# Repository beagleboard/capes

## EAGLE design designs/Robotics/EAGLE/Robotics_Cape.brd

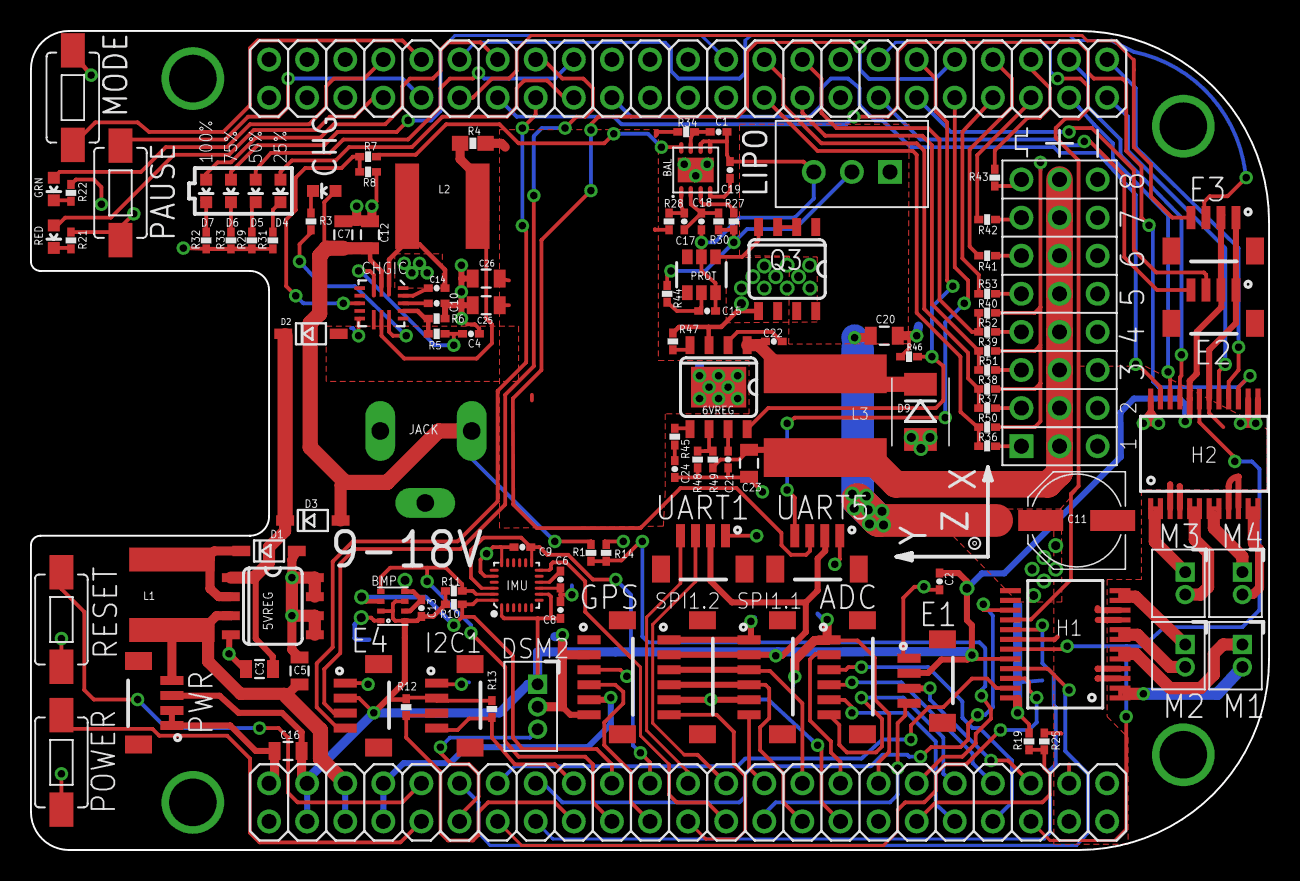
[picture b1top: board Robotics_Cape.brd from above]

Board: 2 copper layers, 82.5 x 54.6 mm, 119 parts (0 on the bottom side), 122 nets.

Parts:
5VREG: AP1509SOIC-8-TIGHT; SO08-TIGHT
6VREG: AOZ1284; SO08-EXPOSED
ADC: JST_SH_6
BAL: BQ29209; 8-SON_3X3MM
BBB_HEADERS: BEAGLEBONE_OUTLINE; BEAGLEBONE_SHIELD
BMP: BMP280
C1, C2, C6, C8, C9, C13, C14, C15, C17, C18, C19, C21, C22, C24: 0.1uF; 0402-CAP
C3, C5, C7, C12, C16, C20, C23, C25, C26: 10uF 25V; 0805
C4, C10: 1uF; 0402-CAP
C11: 100uF 16V; PANASONIC_D
CHG: GRN; LED-0603
CHGIC: MP2615
D1, D2, D3: SOD-123
D4: RED; LED-0603
D5, D6, D7: GREEN; LED-0603
D9: DO-214AA
DSM2: JST_ZH_3
E1, E2, E3, E4: JST_SH_4; JST_SH_4_SMD
E$1: BATTERY_INDICATOR
GPS: JST_SH_6
GRN: GRN; LED-0603
H1, H2: TB6621FNG; SSOP24
I2C1: JST_SH_4; JST_SH_4_SMD
IMU: MPU-9250; QFN24G-0.4-3X3MM
JACK: 5.5x2.1mm; DCJ0303
L1, L2: 6.8uH; TAIYO_NRS
L3: 3.3uH; 8X8MM_INDUCTOR
LIPO: JST_XH_3-PIN
M1, M2, M3, M4: JST_ZH_2
MODE: SWITCH-MOMENTARY-2-SMD-1101NE; TACTILE-SWITCH-1101NE
PAUSE: SWITCH-MOMENTARY-2-SMD-1101NE; TACTILE-SWITCH-1101NE
POWER: SWITCH-MOMENTARY-2-SMD-1101NE; TACTILE-SWITCH-1101NE
PROT: S-8261; SOT-236
PWR: JST_SH_4; JST_SH_4_SMD
Q3: MOSFET-N; SO08-TIGHT
R1, R19, R45: 47k; 0402-RES
R3, R44: 1k; 0402-RES
R4: 0.1; 0603-RES
R5, R6, R8, R48: 10k; 0402-RES
R7, R10, R11, R12, R13, R14, R25, R36, R37, R38, R39, R40, R41, R42, R43, R50, R51, R52, R53: 4.7k; 0402-RES
R21, R22, R29, R30, R31, R32, R33: 261; 0402-RES
R27, R28, R34: 160; 0402-RES
R46: 1K; 0402-RES
R47: 100k; 0402-RES
R49: 65k; 0402-RES
RED: RED; LED-0603
RESET: SWITCH-MOMENTARY-2-SMD-1101NE; TACTILE-SWITCH-1101NE
SPI1.1, SPI1.2: JST_SH_6
U$1: SERVO_HEADERS_8X; 3X8_0.1"_HEADER
U$5: XYZ_BIG
UART1, UART5: JST_SH_4; JST_SH_4_SMD

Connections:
3.3V: BBB_HEADERS.49, BBB_HEADERS.50, BMP.2, BMP.6, BMP.8, C2.2, C8.1, C9.2, C13.1, C16.1, DSM2.P$1, E1.2, E2.2, E3.2, E4.2, H1.20, H2.20, I2C1.2, IMU.1, IMU.8, IMU.13, IMU.22, PWR.3, R10.1, R11.2, R12.2, R13.1, SPI1.1.2, SPI1.2.2, UART1.2, UART5.2
5.0V: 5VREG.3, BBB_HEADERS.51, BBB_HEADERS.52, C5.1, L1.2, PWR.4
AIN0: ADC.3, BBB_HEADERS.85
AIN1: ADC.4, BBB_HEADERS.86
AIN2: ADC.5, BBB_HEADERS.83
AIN3: ADC.6, BBB_HEADERS.84
BATT_MID: LIPO.P$2, R27.1, R30.1, R44.1
BATT_MINUS: BAL.5, BAL.6, C1.2, C15.1, C18.1, C19.2, LIPO.P$3, PROT.2, PROT.6, Q3.1, Q3.2, Q3.3
CHG_EN: CHGIC.6, R7.2, R8.1
CO: BAL.8, R7.1
DO: PROT.1, Q3.4
GND: 5VREG.4, 5VREG.5, 5VREG.6, 5VREG.7, 5VREG.8, 6VREG.3, ADC.1, BBB_HEADERS.1, BBB_HEADERS.2, BBB_HEADERS.47, BBB_HEADERS.48, BBB_HEADERS.80, BBB_HEADERS.89, BBB_HEADERS.90, BBB_HEADERS.91, BBB_HEADERS.92, BMP.1, BMP.5, BMP.7, C2.1, C3.2, C4.1, C5.2, C6.2, C7.2, C8.2, C9.1, C10.1, C11.-, C12.2, C13.2, C16.2, C20.1, C21.1, C23.1, C24.1, C25.2, C26.2, CHGIC.8, CHGIC.16, D1.A, D9.A, DSM2.P$2, E1.1, E2.1, E3.1, E4.1, GPS.2, GPS.6, H1.3, H1.4, H1.9, H1.10, H1.18, H2.3, H2.4, H2.9, H2.10, H2.18, I2C1.1, IMU.9, IMU.18, IMU.20, JACK.2, JACK.3, MODE.P$1, PAUSE.P$1, POWER.P$1, PWR.1, PWR.2, Q3.5, Q3.6, Q3.7, Q3.8, R6.1, R8.2, R14.2, R21.2, R22.2, R25.2, R29.2, R31.2, R32.2, R33.2, R46.1, R47.1, R48.1, R50.2, R51.2, R52.2, R53.2, RESET.P$1, SPI1.1.1, SPI1.2.1, U$1.P$13, U$1.P$14, U$1.P$15, U$1.P$16, U$1.P$17, U$1.P$18, U$1.P$23, U$1.P$24, UART1.1, UART5.1
I2C1_SCL: BBB_HEADERS.63, I2C1.3, R12.1
I2C1_SDA: BBB_HEADERS.64, I2C1.4, R13.2
I2C2_SCL: BBB_HEADERS.65, BMP.4, IMU.23, R11.1
I2C2_SDA: BBB_HEADERS.66, BMP.3, IMU.24, R10.2
IMU_INT: BBB_HEADERS.71, IMU.12
L3: D6.C, R33.1
L4: D7.C, R32.1
LED_1: BBB_HEADERS.17, D4.A
LED_2: BBB_HEADERS.18, D5.A
LED_3: BBB_HEADERS.26, D6.A
LED_4: BBB_HEADERS.14, D7.A
LED_GRN: BBB_HEADERS.8, GRN.A
LED_RED: BBB_HEADERS.7, RED.A
MDIR_1A: BBB_HEADERS.58, H1.21
MDIR_1B: BBB_HEADERS.59, H1.22
MDIR_2A: BBB_HEADERS.61, H1.17
MDIR_2B: BBB_HEADERS.34, H1.16
MDIR_3A: BBB_HEADERS.44, H2.21
MDIR_3B: BBB_HEADERS.43, H2.22
MDIR_4A: BBB_HEADERS.45, H2.17
MDIR_4B: BBB_HEADERS.46, H2.16
MODE_BTN: BBB_HEADERS.10, MODE.P$2
MOT1A: H1.1, H1.2, M1.P$2
MOT1B: H1.5, H1.6, M1.P$1
MOT2A: H1.11, H1.12, M2.P$1
MOT2B: H1.7, H1.8, M2.P$2
MOT3A: H2.1, H2.2, M3.P$1
MOT3B: H2.5, H2.6, M3.P$2
MOT4A: H2.11, H2.12, M4.P$2
MOT4B: H2.7, H2.8, M4.P$1
MOT_STBY: BBB_HEADERS.87, H1.19, H2.19
unnamed: R36.2, U$1.P$1
unnamed: GRN.C, R22.1
unnamed: BAL.2, C17.1, C18.2, R30.2
unnamed: R21.1, RED.C
unnamed: BAL.1, C17.2, R28.2
unnamed: 6VREG.7, C21.2
unnamed: C15.2, PROT.5, R44.2
unnamed: C6.1, IMU.10
unnamed: C14.1, CHGIC.15
unnamed: 5VREG.2, D1.C, L1.1
unnamed: CHG.C, R3.2
unnamed: CHGIC.11, R3.1
unnamed: BAL.4, C19.1
unnamed: R37.2, U$1.P$2
unnamed: BAL.7, C1.1, R34.2
unnamed: R38.2, U$1.P$3
unnamed: R39.2, U$1.P$4
unnamed: D5.C, R29.1
unnamed: D4.C, R31.1
unnamed: BAL.3, R27.2
unnamed: R40.2, U$1.P$5
unnamed: R41.2, U$1.P$6
unnamed: 6VREG.2, C22.1
unnamed: R42.2, U$1.P$19
unnamed: C14.2, CHGIC.1, L2.1
unnamed: R43.2, U$1.P$20
unnamed: 6VREG.1, C22.2, D9.C, L3.1
unnamed: 6VREG.4, R47.2
unnamed: C23.2, L3.2, R49.2, U$1.P$7, U$1.P$8, U$1.P$9, U$1.P$10, U$1.P$11, U$1.P$12, U$1.P$21, U$1.P$22
unnamed: 6VREG.5, R45.2
unnamed: 6VREG.6, R48.2, R49.1
unnamed: C24.2, R45.1
unnamed: CHGIC.10, L2.2, R4.2
unnamed: C10.2, CHGIC.14
unnamed: CHGIC.13, R5.1, R6.2
unnamed: 5VREG.1, C3.1, D2.C, D3.C
PAUSE_BTN: BBB_HEADERS.9, PAUSE.P$2
PWM_1A: BBB_HEADERS.60, H1.23
PWM_1B: BBB_HEADERS.62, H1.15
PWM_2A: BBB_HEADERS.19, H2.23
PWM_2B: BBB_HEADERS.13, H2.15
PWR: BBB_HEADERS.55, POWER.P$2
QEP_0A: BBB_HEADERS.88, E1.3
QEP_0B: BBB_HEADERS.73, E1.4
QEP_1A: BBB_HEADERS.35, E2.3
QEP_1B: BBB_HEADERS.33, E2.4
QEP_2A: BBB_HEADERS.12, E3.3
QEP_2B: BBB_HEADERS.11, E3.4
QEP_4A: BBB_HEADERS.16, E4.3
QEP_4B: BBB_HEADERS.15, E4.4
RESET: BBB_HEADERS.56, RESET.P$2
SERVO_EN: 6VREG.8, BBB_HEADERS.36, R46.2
SPI1_MISO: BBB_HEADERS.75, SPI1.1.4, SPI1.2.4
SPI1_MOSI: BBB_HEADERS.76, SPI1.1.3, SPI1.2.3
SPI1_SCK: BBB_HEADERS.77, SPI1.1.5, SPI1.2.5
SPI1_SS1: BBB_HEADERS.74, SPI1.1.6
SPI1_SS2: BBB_HEADERS.69, SPI1.2.6
SVO1: BBB_HEADERS.27, R36.1, R50.1
SVO2: BBB_HEADERS.28, R37.1, R51.1
SVO3: BBB_HEADERS.29, R38.1, R52.1
SVO4: BBB_HEADERS.30, R39.1, R53.1
SVO5: BBB_HEADERS.39, R40.1
SVO6: BBB_HEADERS.40, R41.1
SVO7: BBB_HEADERS.41, R42.1
SVO8: BBB_HEADERS.42, R43.1
SYS_5V: BBB_HEADERS.53, BBB_HEADERS.54, GPS.5
UART1_RX: BBB_HEADERS.72, UART1.3
UART1_TX: BBB_HEADERS.70, UART1.4
UART2_RX: BBB_HEADERS.68, GPS.3
UART2_TX: BBB_HEADERS.67, GPS.4
UART4_RX: BBB_HEADERS.57, DSM2.P$3
UART5_RX: BBB_HEADERS.38, UART5.3
UART5_TX: BBB_HEADERS.37, UART5.4
VCC: C7.1, C12.1, CHG.A, CHGIC.2, D3.A, JACK.1, R1.1
VCC_CHG: C4.2, CHGIC.3, R5.2
VDD_ADC: ADC.2, BBB_HEADERS.78
V_BATT: 6VREG.9, C11.+, C20.2, C25.1, C26.1, CHGIC.9, D2.A, H1.13, H1.14, H1.24, H2.13, H2.14, H2.24, LIPO.P$1, R4.1, R19.1, R28.1, R34.1
V_DIV_BAT: BBB_HEADERS.81, R19.2, R25.1
V_DIV_DC: BBB_HEADERS.82, R1.2, R14.1

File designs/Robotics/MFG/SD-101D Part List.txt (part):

Partlist

Exported from SD-101D Robotics Cape.brd at 5/12/17 4:58 AM

EAGLE Version 8.2.0 Copyright (c) 1988-2017 Autodesk, Inc.

Assembly variant: 

Part        Value                         Package               Library                    Position (inch)       Orientation

5VREG       AP1509SOIC-8-TIGHT            SO08-TIGHT            Strawson_Eagle_Lib         (0.785 0.64)          R270
6VREG       AOZ1284                       SO08-EXPOSED          Strawson_Eagle_Lib         (1.955 1.215)         R180
ADC         JST_SH_6                      JST_SH_6              Strawson_Eagle_Lib         (2.245 0.355)         R90
BAL         BQ29209                       8-SON_3X3MM           Strawson_Eagle_Lib         (1.895 1.785)         R0
BBB_HEADERS BEAGLEBONE_OUTLINE            BEAGLEBONE_SHIELD     Strawson_Eagle_Lib         (0 2.15)              R270
BMP         BMP280                        BMP280                Strawson_Eagle_Lib         (1.1 0.64)            R180
C1          0.1uF                         0402-CAP              Strawson_Eagle_Lib         (1.955 1.885)         R0
C2          0.1uF                         0402-CAP              Strawson_Eagle_Lib         (2.535 0.705)         R90
C3          10uF 25V                      0805                  SparkFun-Capacitors        (0.75 0.475)          R180
C4          1uF                           0402-CAP              Strawson_Eagle_Lib         (1.305 1.355)         R180
C5          10uF 25V                      0805                  SparkFun-Capacitors        (0.855 0.47)          R90
C6          0.1uF                         0402-CAP              Strawson_Eagle_Lib         (1.54 0.71)           R270
C7          10uF 25V                      0805                  SparkFun-Capacitors        (0.97 1.615)          R90
C8          0.1uF                         0402-CAP              Strawson_Eagle_Lib         (1.54 0.63)           R90
C9          0.1uF                         0402-CAP              Strawson_Eagle_Lib         (1.44 0.795)          R0
C10         1uF                           0402-CAP              Strawson_Eagle_Lib         (1.215 1.435)         R180
C11         100uF 16V                     PANASONIC_D           adafruit                   (2.895 0.865)         R180
C12         10uF 25V                      0805                  SparkFun-Capacitors        (1.04 1.615)          R90
C13         0.1uF                         0402-CAP              Strawson_Eagle_Lib         (1.175 0.635)         R90
C14         0.1uF                         0402-CAP              Strawson_Eagle_Lib         (1.215 1.475)         R0
C15         0.1uF                         0402-CAP              Strawson_Eagle_Lib         (1.925 1.415)         R180
C16         10uF 25V                      0805                  SparkFun-Capacitors        (0.825 0.26)          R180
C17         0.1uF                         0402-CAP              Strawson_Eagle_Lib         (1.865 1.65)          R90
C18         0.1uF                         0402-CAP              Strawson_Eagle_Lib         (1.91 1.65)           R90
C19         0.1uF                         0402-CAP              Strawson_Eagle_Lib         (1.985 1.785)         R90
C20         10uF 25V                      0805                  SparkFun-Capacitors        (2.39 1.35)           R180
C21         0.1uF                         0402-CAP              Strawson_Eagle_Lib         (1.98 1.025)          R90
C22         0.1uF                         0402-CAP              Strawson_Eagle_Lib         (2.1 1.335)           R180
C23         10uF 25V                      0805                  SparkFun-Capacitors        (2.035 1.015)         R90
C24         0.1uF                         0402-CAP              Strawson_Eagle_Lib         (1.84 1)              R90
C25         10uF 25V                      0805                  SparkFun-Capacitors        (1.345 1.43)          R180
C26         10uF 25V                      0805                  SparkFun-Capacitors        (1.345 1.5)           R180
CHG         GRN                           LED-0603              SparkFun-LED               (0.92 1.73)           R90
CHGIC       MP2615                        MP2615                Strawson_Eagle_Lib         (1.07 1.435)          R270
D1                                        SOD-123               adafruit                   (0.775 0.785)         R0
D2                                        SOD-123               adafruit                   (0.885 1.355)         R0
D3                                        SOD-123               adafruit                   (0.89 0.865)          R0
D4          RED                           LED-0603              SparkFun-LED               (0.805 1.73)          R180
D5          GREEN                         LED-0603              SparkFun-LED               (0.74 1.73)           R180
D6          GREEN                         LED-0603              SparkFun-LED               (0.675 1.73)          R180
D7          GREEN                         LED-0603              SparkFun-LED               (0.61 1.73)           R180
D9                                        DO-214AA              Strawson_Eagle_Lib         (2.485 1.15)          R270
DSM2        JST_ZH_3                      JST_ZH_3              Strawson_Eagle_Lib         (1.48 0.435)          R270
E1          JST_SH_4                      JST_SH_4_SMD          Strawson_Eagle_Lib         (2.505 0.485)         R90
E2          JST_SH_4                      JST_SH_4_SMD          Strawson_Eagle_Lib         (3.295 1.42)          R0
E3          JST_SH_4                      JST_SH_4_SMD          Strawson_Eagle_Lib         (3.295 1.61)          R0
E4          JST_SH_4                      JST_SH_4_SMD          Strawson_Eagle_Lib         (1.025 0.42)          R90
GPS         JST_SH_6                      JST_SH_6              Strawson_Eagle_Lib         (1.615 0.355)         R90
GRN         GRN                           LED-0603              SparkFun-LED               (0.21 1.735)          R180
H1          TB6621FNG                     SSOP24                SparkFun                   (2.865 0.54)          R90
H2          TB6621FNG                     SSOP24                SparkFun                   (3.23 1.04)           R0
I2C1        JST_SH_4                      JST_SH_4_SMD          Strawson_Eagle_Lib         (1.265 0.42)          R90
IMU         MPU-9250                      QFN24G-0.4-3X3MM      Strawson_Eagle_Lib         (1.425 0.695)         R90
JACK        5.5x2.1mm                     DCJ0303               Strawson_Eagle_Lib         (1.185 1.1)           R270
L1          6.8uH                         TAIYO_NRS             Strawson_Eagle_Lib         (0.52 0.67)           R270
L2          6.8uH                         TAIYO_NRS             Strawson_Eagle_Lib         (1.23 1.69)           R0
L3          3.3uH                         8X8MM_INDUCTOR        Strawson_Eagle_Lib         (2.235 1.14)          R270
LIPO                                      JST_XH_3-PIN          Strawson_Eagle_Lib         (2.405 1.78)          R270
M1          JST_ZH_2                      JST_ZH_2              Strawson_Eagle_Lib         (3.33 0.51)           R270
M2          JST_ZH_2                      JST_ZH_2              Strawson_Eagle_Lib         (3.18 0.51)           R270
M3          JST_ZH_2                      JST_ZH_2              Strawson_Eagle_Lib         (3.18 0.7)            R270
M4          JST_ZH_2                      JST_ZH_2              Strawson_Eagle_Lib         (3.33 0.7)            R270
MODE        SWITCH-MOMENTARY-2-SMD-1101NE TACTILE-SWITCH-1101NE SparkFun-Electromechanical (0.26 1.975)          R270
PAUSE       SWITCH-MOMENTARY-2-SMD-1101NE TACTILE-SWITCH-1101NE SparkFun-Electromechanical (0.385 1.725)         R90
POWER       SWITCH-MOMENTARY-2-SMD-1101NE TACTILE-SWITCH-1101NE SparkFun-Electromechanical (0.23 0.23)           R90
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
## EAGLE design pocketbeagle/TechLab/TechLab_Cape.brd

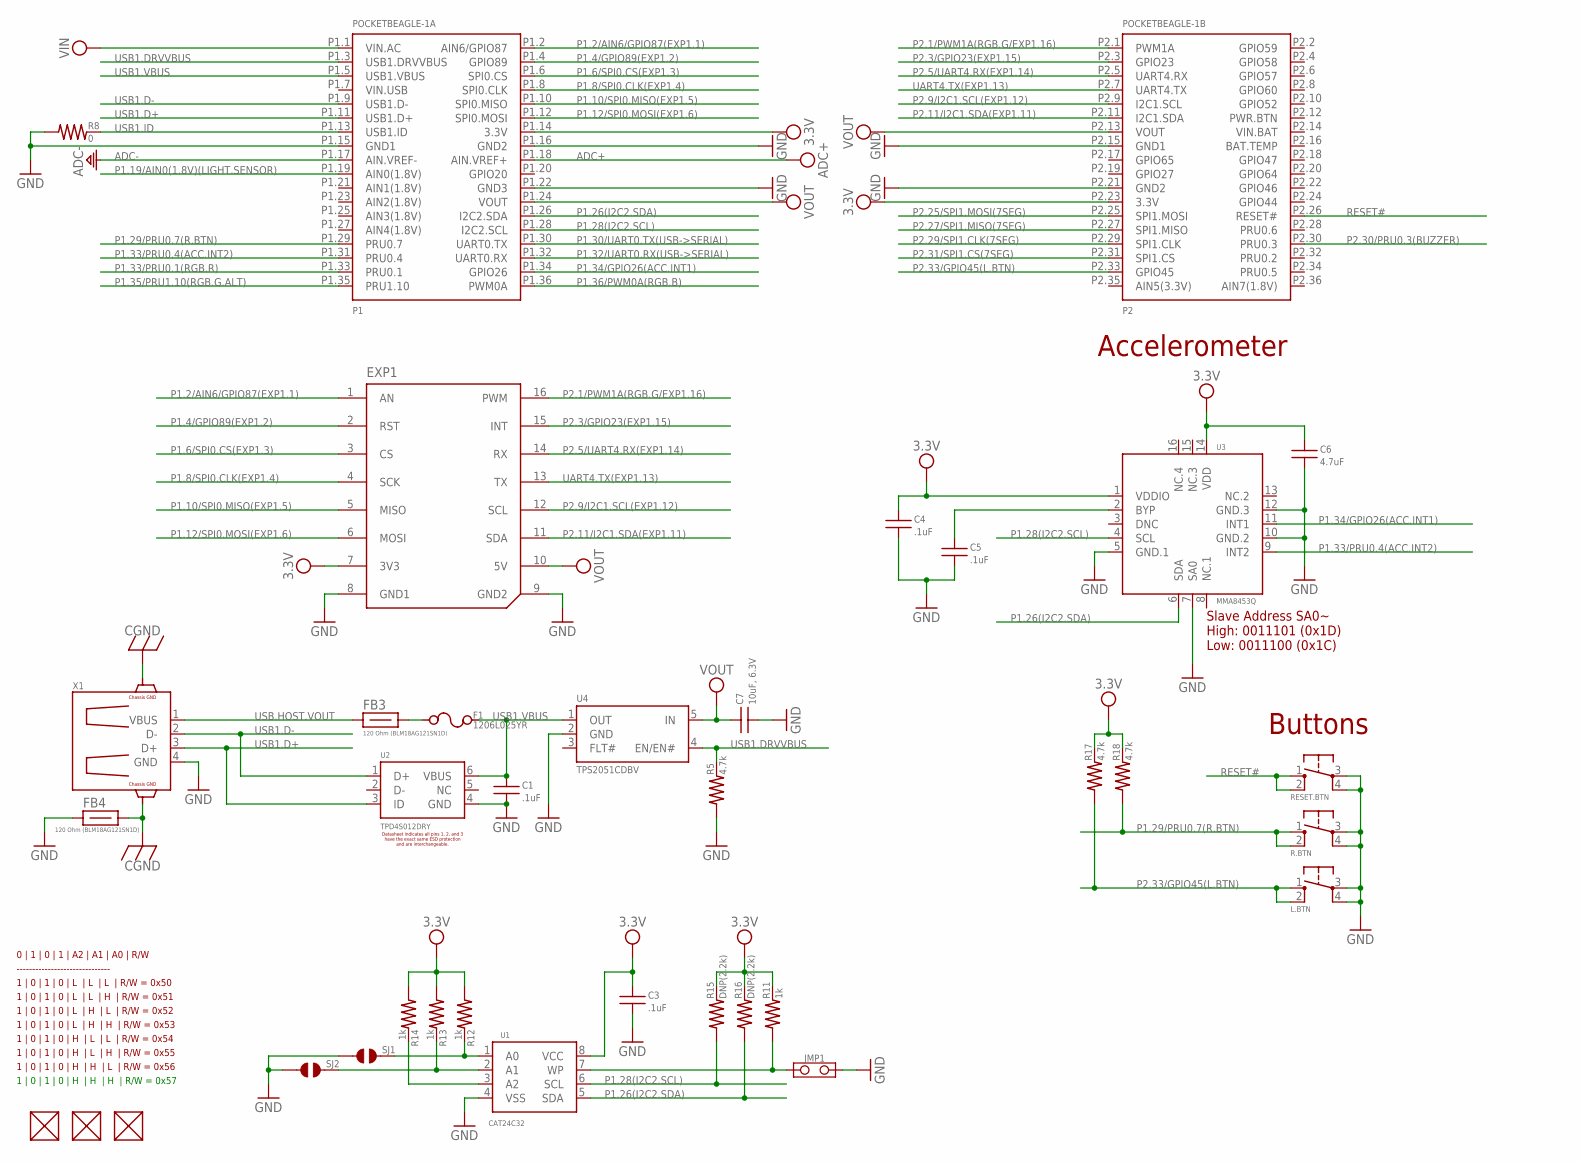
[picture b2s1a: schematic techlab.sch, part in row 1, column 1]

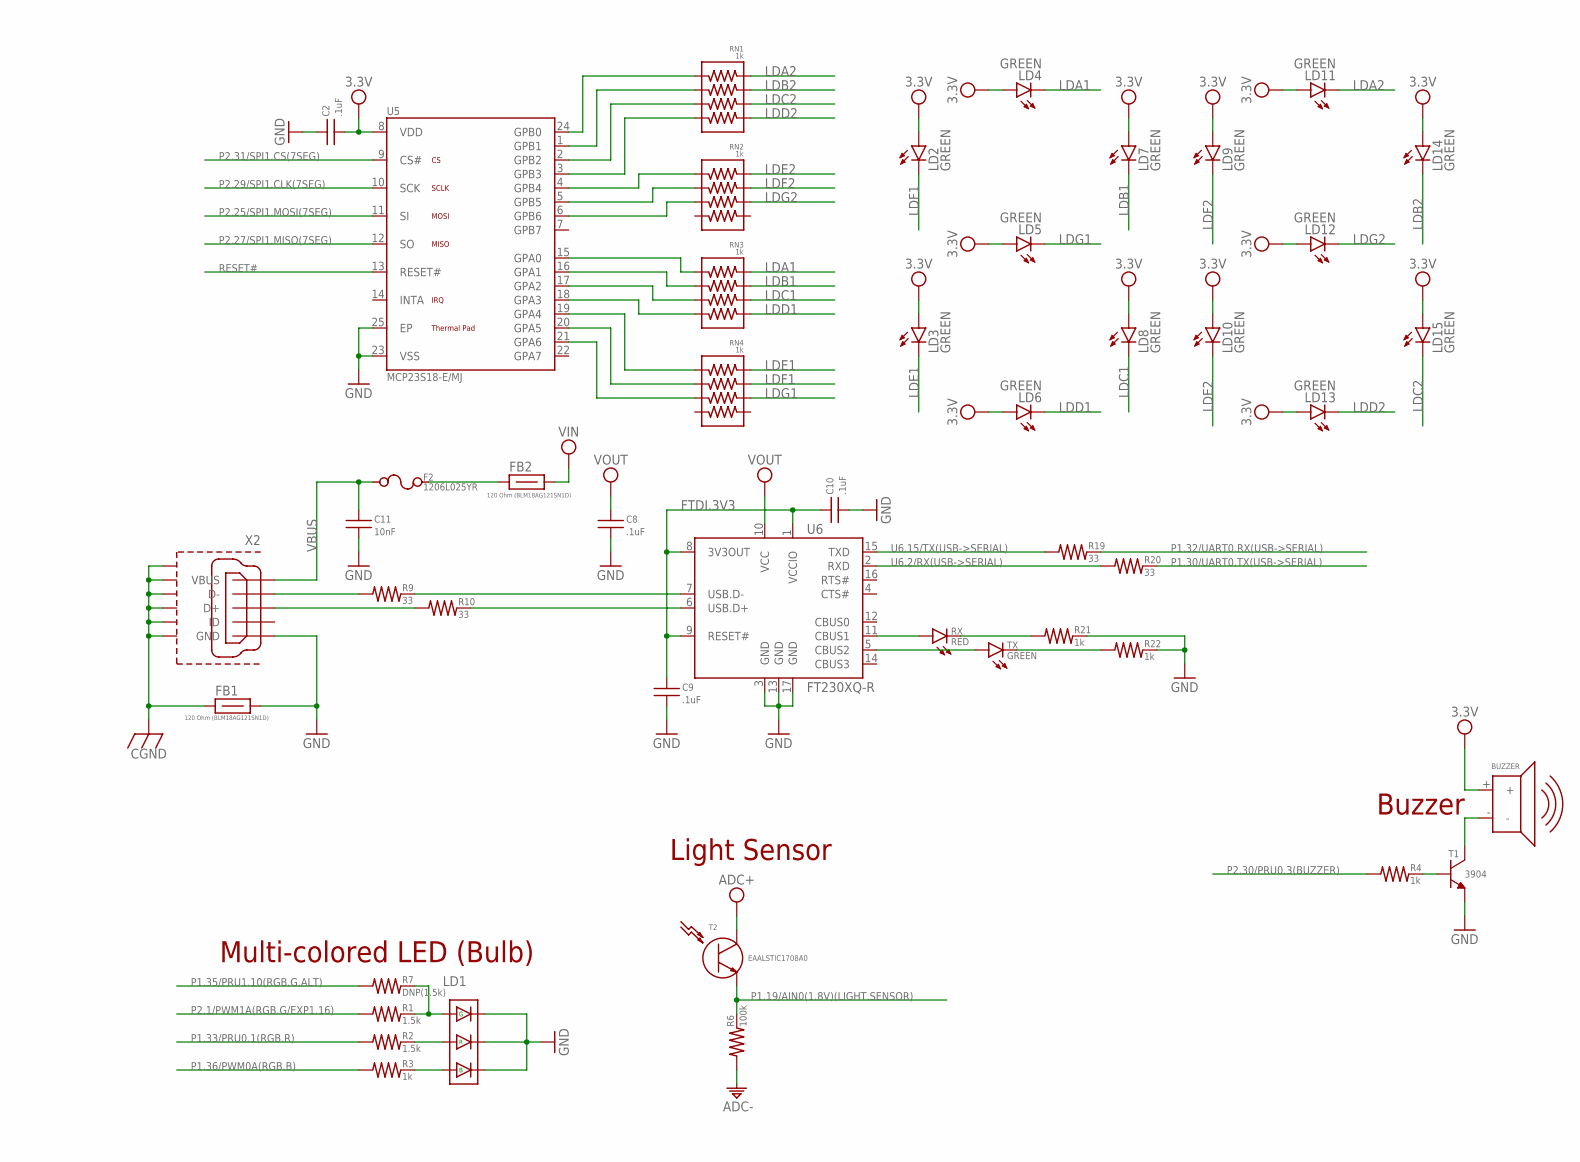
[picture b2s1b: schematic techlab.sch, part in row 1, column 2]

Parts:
BUZZER: SMD-140035H
C1, C2, C3, C4, C5, C8, C9, C10: .1uF; 0402
C6: 4.7uF; 0402
C7: 10uF, 6.3V; 0805
C11: 10nF; 0402
EXP1: PARALLEL-8PIN-0.9INCH_PITCH-SMT_GP
F1, F2: 1206L025YR; 1206
FB1, FB2, FB3, FB4: 120 Ohm (BLM18AG121SN1D); 0603
FUD1, FUD2, FUD3: FIDUCIAL; FIDUCIAL_40MIL
JMP1: JUMPER-(X2)
L.BTN: TACTILE.SWITCH-6MM; 6MM_TACTILE-SWITCH
LD1: JNS-5050RGB; LED_RGB_5050
LD2, LD3, LD4, LD5, LD6, LD7, LD8, LD9, LD10, LD11, LD12, LD13, LD14, LD15: GREEN; 0805-LED
POCKETBEAGLE-1: POCKETBEAGLE-(ORIGIN-CENTER)-SMT.PADS(ONLY)-NO.RE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; POCKETBEAGLE-(ORIGIN-CENTER)-SMT.PADS(ONLY)-NO.RESTRICT
R1, R2: 1.5k; 0402
R3, R4, R11, R12, R13, R14, R21, R22: 1k; 0402
R5, R17, R18: 4.7k; 0402
R6: 100k; 0402
R7: DNP(1.5k); 0402
R8: 0; 0402
R9, R10, R19, R20: 33; 0402
R15, R16: DNP(2.2k); 0402
R.BTN: TACTILE.SWITCH-6MM; 6MM_TACTILE-SWITCH
RESET.BTN: TACTILE.SWITCH-3X3.5MM; 3X3.5MM-TACTILE-SWITCH
RN1, RN2, RN3, RN4: 1k; RN0804
RX: RED; 0805-LED
SJ1, SJ2: SOLDER.JOINT-(INCH)-0402; SOLDER.JOINT(0402)
T1: 3904; SOT23
T2: EAALSTIC1708A0
TX: GREEN; 0805-LED
U1: CAT24C32; UDFN8,2X3(ON-SEMI)
U2: TPD4S012DRY; SON-6(TI)-DRY
U3: MMA8453Q; QFN-16-(MMA8453Q)
U4: TPS2051CDBV; SOT23-5(TI-DBV)
U5: MCP23S18-E/MJ; QFN24-MJ-0.5-4X4MM
U6: FT230XQ-R; QFN16-0.65-4X4MM
X1: 292303-1
X2: 10118192-0001LF; 10118192-0001LF(MICRO-USB-B-AMPHENOL-FCI)

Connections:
3.3V: BUZZER.+, C2.2, C3.1, C4.1, C6.1, EXP1.7 (3V3), LD2.A, LD3.A, LD4.A, LD5.A, LD6.A, LD7.A, LD8.A, LD9.A, LD10.A, LD11.A, LD12.A, LD13.A, LD14.A, LD15.A, POCKETBEAGLE-1.P1.14 (3.3V), POCKETBEAGLE-1.P2.23 (3.3V), R11.2, R12.1, R13.1, R14.1, R15.2, R16.2, R17.2, R18.2, U1.8 (VCC), U3.1 (VDDIO), U3.14 (VDD), U5.8 (VDD)
A0: R12.2, SJ1.2, U1.1 (A0)
A1: R13.2, SJ2.2, U1.2 (A1)
A2: R14.2, U1.3 (A2)
ADC+: POCKETBEAGLE-1.P1.18 (AIN.VREF+), T2.1 (C)
ADC-: POCKETBEAGLE-1.P1.17 (AIN.VREF-), R6.1
CGND: FB1.1, FB4.2, X1.C1 (CG), X1.C2 (CG), X2.CGND1 (SGND1), X2.CGND2 (SGND2), X2.CGND3 (SGND3), X2.CGND4 (SGND4), X2.CGND5 (SGND5), X2.CGND6 (SGND6)
F2-FB2: F2.2, FB2.1
FB4-F1: F1.1, FB3.2
FTDI.3V3: C9.1, C10.1, U6.1 (VCCIO), U6.8 (3V3OUT), U6.9 (RESET#)
GND: C1.2, C2.1, C3.2, C4.2, C5.2, C6.2, C7.2, C8.2, C9.2, C10.2, C11.2, EXP1.8 (GND1), EXP1.9 (GND2), FB1.2, FB4.1, JMP1.2, L.BTN.3, L.BTN.4, LD1.4(-), LD1.5(-), LD1.6(-), POCKETBEAGLE-1.P1.15 (GND1), POCKETBEAGLE-1.P1.16 (GND2), POCKETBEAGLE-1.P1.22 (GND3), POCKETBEAGLE-1.P2.15 (GND1), POCKETBEAGLE-1.P2.21 (GND2), R5.1, R8.1, R21.2, R22.2, R.BTN.3, R.BTN.4, RESET.BTN.3, RESET.BTN.4, SJ1.1, SJ2.1, T1.2 (E), U1.4 (VSS), U2.4 (GND), U3.5 (GND.1), U3.7 (SA0), U3.10 (GND.2), U3.12 (GND.3), U4.2 (GND), U5.23 (VSS), U5.25 (EP), U6.3 (GND), U6.13 (GND), U6.17 (GND), X1.4 (GND), X2.GND
GPA0: RN3.8, U5.15 (GPA0)
GPA1: RN3.7, U5.16 (GPA1)
GPA2: RN3.6, U5.17 (GPA2)
GPA3: RN3.5, U5.18 (GPA3)
GPA4: RN4.8, U5.19 (GPA4)
GPA5: RN4.7, U5.20 (GPA5)
GPA6: RN4.6, U5.21 (GPA6)
GPB0: RN1.8, U5.24 (GPB0)
GPB1: RN1.7, U5.1 (GPB1)
GPB2: RN1.6, U5.2 (GPB2)
GPB3: RN1.5, U5.3 (GPB3)
GPB4: RN2.8, U5.4 (GPB4)
GPB5: RN2.7, U5.5 (GPB5)
GPB6: RN2.6, U5.6 (GPB6)
LDA1: LD4.K, RN3.1
LDA2: LD11.K, RN1.1
LDB1: LD7.K, RN3.2
LDB2: LD14.K, RN1.2
LDC1: LD8.K, RN3.3
LDC2: LD15.K, RN1.3
LDD1: LD6.K, RN3.4
LDD2: LD13.K, RN1.4
LDE1: LD3.K, RN4.1
LDE2: LD10.K, RN2.1
LDF1: LD2.K, RN4.2
LDF2: LD9.K, RN2.2
LDG1: LD5.K, RN4.3
LDG2: LD12.K, RN2.3
LED.BLUE: LD1.1(+), R3.2
LED.GREEN: LD1.3(+), R1.2, R7.2
LED.RED: LD1.2(+), R2.2
unnamed: BUZZER.-, T1.3 (C)
unnamed: C5.1, U3.2 (BYP)
unnamed: R4.2, T1.1 (B)
P1.2/AIN6/GPIO87(EXP1.1): EXP1.1 (AN), POCKETBEAGLE-1.P1.2 (AIN6/GPIO87)
P1.4/GPIO89(EXP1.2): EXP1.2 (RST), POCKETBEAGLE-1.P1.4 (GPIO89)
P1.6/SPI0.CS(EXP1.3): EXP1.3 (CS), POCKETBEAGLE-1.P1.6 (SPI0.CS)
P1.8/SPI0.CLK(EXP1.4): EXP1.4 (SCK), POCKETBEAGLE-1.P1.8 (SPI0.CLK)
P1.10/SPI0.MISO(EXP1.5): EXP1.5 (MISO), POCKETBEAGLE-1.P1.10 (SPI0.MISO)
P1.12/SPI0.MOSI(EXP1.6): EXP1.6 (MOSI), POCKETBEAGLE-1.P1.12 (SPI0.MOSI)
P1.19/AIN0(1.8V)(LIGHT.SENSOR): POCKETBEAGLE-1.P1.19 (AIN0(1.8V)), R6.2, T2.2 (E)
P1.26(I2C2.SDA): POCKETBEAGLE-1.P1.26 (I2C2.SDA), R16.1, U1.5 (SDA), U3.6 (SDA)
P1.28(I2C2.SCL): POCKETBEAGLE-1.P1.28 (I2C2.SCL), R15.1, U1.6 (SCL), U3.4 (SCL)
P1.29/PRU0.7(R.BTN): POCKETBEAGLE-1.P1.29 (PRU0.7), R18.1, R.BTN.1, R.BTN.2
P1.30/UART0.TX(USB->SERIAL): POCKETBEAGLE-1.P1.30 (UART0.TX), R20.2
P1.32/UART0.RX(USB->SERIAL): POCKETBEAGLE-1.P1.32 (UART0.RX), R19.2
P1.33/PRU0.1(RGB.R): POCKETBEAGLE-1.P1.33 (PRU0.1), R2.1
P1.33/PRU0.4(ACC.INT2): POCKETBEAGLE-1.P1.31 (PRU0.4), U3.9 (INT2)
P1.34/GPIO26(ACC.INT1): POCKETBEAGLE-1.P1.34 (GPIO26), U3.11 (INT1)
P1.35/PRU1.10(RGB.G.ALT): POCKETBEAGLE-1.P1.35 (PRU1.10), R7.1
P1.36/PWM0A(RGB.B): POCKETBEAGLE-1.P1.36 (PWM0A), R3.1
P2.1/PWM1A(RGB.G/EXP1.16): EXP1.16 (PWM), POCKETBEAGLE-1.P2.1 (PWM1A), R1.1
P2.3/GPIO23(EXP1.15): EXP1.15 (INT), POCKETBEAGLE-1.P2.3 (GPIO23)
P2.5/UART4.RX(EXP1.14): EXP1.14 (RX), POCKETBEAGLE-1.P2.5 (UART4.RX)
P2.9/I2C1.SCL(EXP1.12): EXP1.12 (SCL), POCKETBEAGLE-1.P2.9 (I2C1.SCL)
P2.11/I2C1.SDA(EXP1.11): EXP1.11 (SDA), POCKETBEAGLE-1.P2.11 (I2C1.SDA)
P2.25/SPI1.MOSI(7SEG): POCKETBEAGLE-1.P2.25 (SPI1.MOSI), U5.11 (SI)
P2.27/SPI1.MISO(7SEG): POCKETBEAGLE-1.P2.27 (SPI1.MISO), U5.12 (SO)
P2.29/SPI1.CLK(7SEG): POCKETBEAGLE-1.P2.29 (SPI1.CLK), U5.10 (SCK)
P2.30/PRU0.3(BUZZER): POCKETBEAGLE-1.P2.30 (PRU0.3), R4.1
P2.31/SPI1.CS(7SEG): POCKETBEAGLE-1.P2.31 (SPI1.CS), U5.9 (CS#)
P2.33/GPIO45(L.BTN): L.BTN.1, L.BTN.2, POCKETBEAGLE-1.P2.33 (GPIO45), R17.1
RESET#: POCKETBEAGLE-1.P2.26 (RESET#), RESET.BTN.1, RESET.BTN.2, U5.13 (RESET#)
RX->R21: R21.1, RX.K
TX->R22: R22.1, TX.K
U6.2/RX(USB->SERIAL): R20.1, U6.2 (RXD)
U6.5->TX: TX.A, U6.5 (CBUS2)
U6.11->RX: RX.A, U6.11 (CBUS1)
U6.15/TX(USB->SERIAL): R19.1, U6.15 (TXD)
UART4.TX(EXP1.13): EXP1.13 (TX), POCKETBEAGLE-1.P2.7 (UART4.TX)
UD+: R10.2, U6.6 (USB.D+)
UD-: R9.2, U6.7 (USB.D-)
USB1.D+: POCKETBEAGLE-1.P1.11 (USB1.D+), U2.3 (ID), X1.3 (D+)
USB1.D-: POCKETBEAGLE-1.P1.9 (USB1.D-), U2.1 (D+), X1.2 (D-)
USB1.DRVVBUS: POCKETBEAGLE-1.P1.3 (USB1.DRVVBUS), R5.2, U4.4 (EN/EN#)
USB1.ID: POCKETBEAGLE-1.P1.13 (USB1.ID), R8.2
USB1.VBUS: C1.1, F1.2, POCKETBEAGLE-1.P1.5 (USB1.VBUS), U2.6 (VBUS), U4.1 (OUT)
USB.HOST.VOUT: FB3.1, X1.1 (VBUS)
VBUS: C11.1, F2.1, X2.VBUS
VIN: FB2.2, POCKETBEAGLE-1.P1.1 (VIN.AC)
VOUT: C7.1, C8.1, EXP1.10 (5V), POCKETBEAGLE-1.P1.24 (VOUT), POCKETBEAGLE-1.P2.13 (VOUT), U4.5 (IN), U6.10 (VCC)
WP: JMP1.1, R11.1, U1.7 (WP)
XD+: R10.1, X2.D+
XD-: R9.1, X2.D-

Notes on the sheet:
Buzzer
Multi-colored LED (Bulb)
Light Sensor
Buttons
Datasheet indicates all pins 1, 2, and 3 have the exact same ESD protection and are interchangeable.
Slave Address SA0~ High: 0011101 (0x1D) Low: 0011100 (0x1C)
Accelerometer
0 | 1 | 0 | 1 | A2 | A1 | A0 | R/W
1 | 0 | 1 | 0 | L | L | L | R/W = 0x50
------------------------------
1 | 0 | 1 | 0 | L | L | H | R/W = 0x51
1 | 0 | 1 | 0 | L | H | L | R/W = 0x52
1 | 0 | 1 | 0 | L | H | H | R/W = 0x53
1 | 0 | 1 | 0 | H | L | L | R/W = 0x54
1 | 0 | 1 | 0 | H | L | H | R/W = 0x55
1 | 0 | 1 | 0 | H | H | L | R/W = 0x56
1 | 0 | 1 | 0 | H | H | H | R/W = 0x57

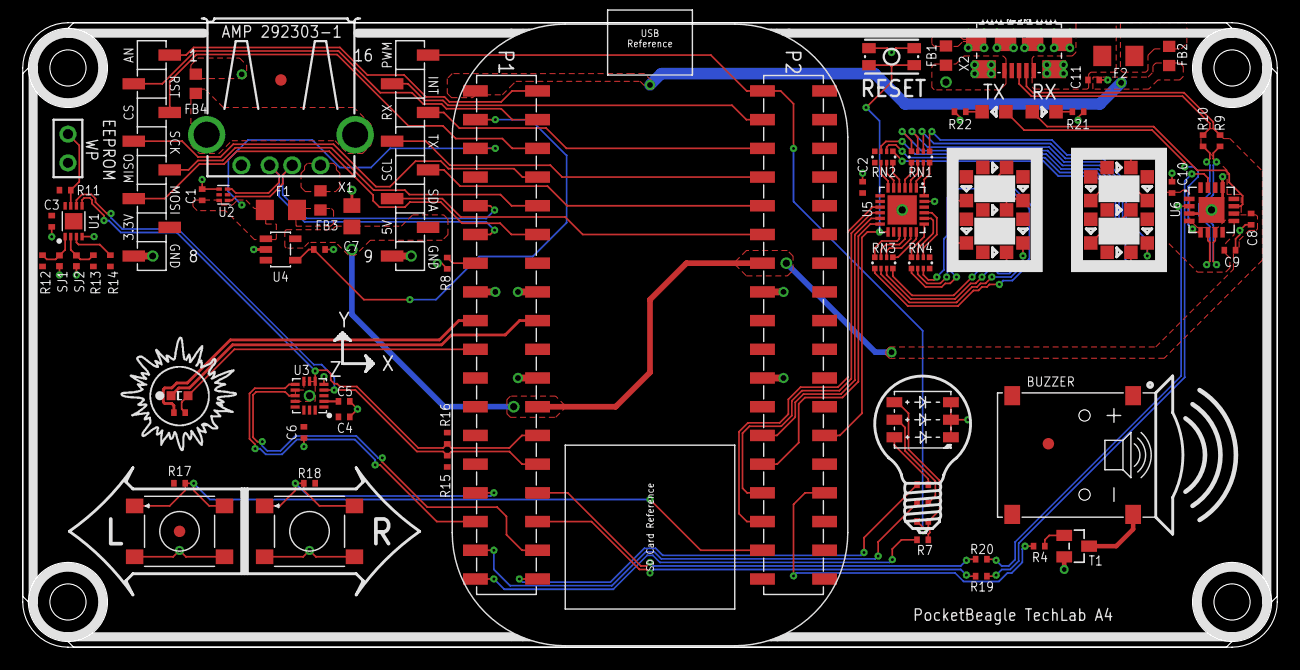
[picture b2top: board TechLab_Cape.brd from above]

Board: 2 copper layers, 111.0 x 55.2 mm, 82 parts (0 on the bottom side), 95 nets.

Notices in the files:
parts and their libraries:
SparkFun-Electromechanical: Licensing: CC v3.0 Share-Alike You are welcome to use this library for commercial purposes.
